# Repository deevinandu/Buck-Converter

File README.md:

# Buck Converter

A DC-DC buck converter system for efficient voltage step-down, controlled via a microcontroller or timer IC.

## Features

- Adjustable output voltage through PWM control
- Efficient power conversion using MOSFET and Schottky diode
- Compact design with Kicad Schematic, PCB layout, and LTspice simulation

## Technologies

This project is built with:

- **Firmware**: Arduino (ESP32 or compatible microcontroller)
- **Hardware Design**: KiCAD (schematic and PCB)
- **Simulation**: LTspice

## Included Files

- **Control Code**: `Buck_Converter.ino` contains the microcontroller code for regulating the buck converter’s output voltage, interfacing with the NE555 timer or directly controlling the IRLZ44N MOSFET.
- **Schematic**: `Buck_Converter_Design.kicad_sch` provides the circuit schematic, including the NE555D timer, IRLZ44N MOSFET, 1N5819 Schottky diode, and 30.5 µH inductor.
- **PCB Layout**: `Buck_Converter.kicad_pcb` includes the PCB design for the buck converter circuit.
- **Simulation**: `Buck_Converter_LTspice_Simulation.asc` is an LTspice simulation file for analyzing the buck converter’s performance, including voltage regulation and switching behavior.

## Installation

Follow these steps to set up the firmware and hardware:

### Firmware

1. Open `Buck_Converter.ino` in the Arduino IDE.
2. Configure pin assignments and PWM parameters for your ESP32 or compatible microcontroller.
3. Upload the code to your microcontroller board.

### Hardware

1. Open `Buck_Converter_Design.kicad_sch` in KiCAD to review the schematic.
2. Use `Buck_Converter.kicad_pcb` to fabricate the PCB or assemble the circuit on a prototyping board.
3. Connect a 24V input power source as indicated in the schematic.

### Simulation

1. Open `Buck_Converter_LTspice_Simulation.asc` in LTspice.
2. Run the simulation to analyze the circuit’s performance, such as output voltage and current characteristics.

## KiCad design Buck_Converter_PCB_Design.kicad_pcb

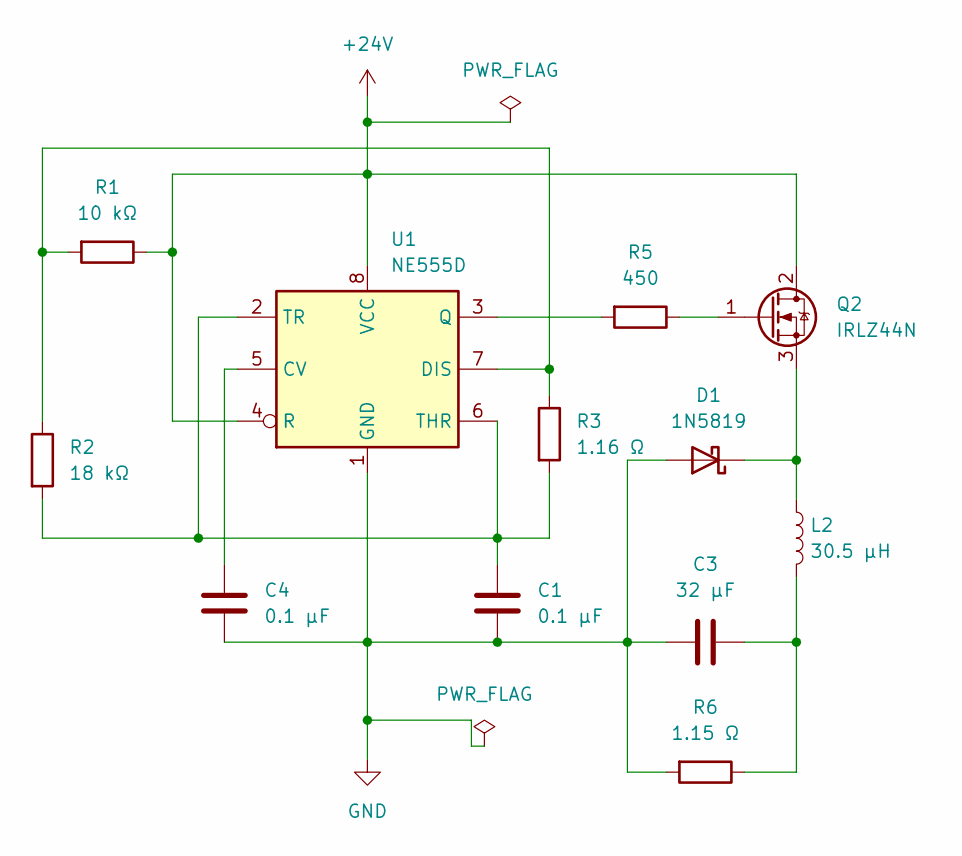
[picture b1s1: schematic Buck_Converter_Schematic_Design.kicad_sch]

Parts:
C1, C4: 0.1 μF; CP_Radial_D5.0mm_P2.50mm
C3: 32 μF; CP_Radial_D5.0mm_P2.50mm
D1: 1N5819; D_DO-41_SOD81_P10.16mm_Horizontal
L2: 30.5 μH; L_Axial_L9.5mm_D4.0mm_P15.24mm_Horizontal_Fastron_SMCC
Q2: IRLZ44N; TO-220-3_Vertical
R1: 10 kΩ; R_1206_3216Metric_Pad1.30x1.75mm_HandSolder
R2: 18 kΩ; R_1206_3216Metric_Pad1.30x1.75mm_HandSolder
R3: 1.16 Ω; R_1206_3216Metric_Pad1.30x1.75mm_HandSolder
R5: 450; R_1206_3216Metric_Pad1.30x1.75mm_HandSolder
R6: 1.15 Ω; R_1206_3216Metric_Pad1.30x1.75mm_HandSolder
U1: NE555D; SOIC-8_3.9x4.9mm_P1.27mm

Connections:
+24V: Q2.2 (D), R1.1, U1.4 (R), U1.8 (VCC)
GND: C1.2, C3.2, C4.2, D1.2 (A), R6.2, U1.1 (GND)
unnamed: C3.1, L2.2, R6.1
unnamed: D1.1 (K), L2.1, Q2.3 (S)
unnamed: Q2.1 (G), R5.1
unnamed: C4.1, U1.5 (CV)
unnamed: R1.2, R2.1, R3.1, U1.7 (DIS)
unnamed: R5.2, U1.3 (Q)
unnamed: C1.1, R2.2, R3.2, U1.2 (TR), U1.6 (THR)

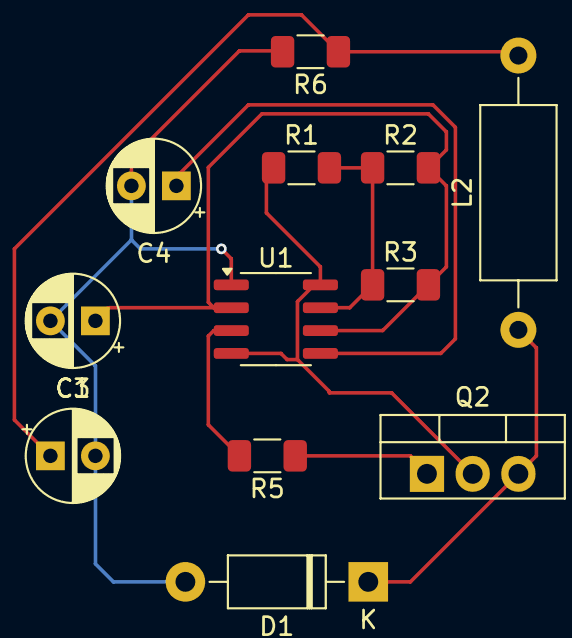
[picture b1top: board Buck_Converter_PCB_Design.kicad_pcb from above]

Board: 2 copper layers, 12 parts (0 on the bottom side), 9 nets.

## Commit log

2025-05-15 README.md
